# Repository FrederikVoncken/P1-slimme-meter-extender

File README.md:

# P1-slimme-meter-extender
Extending the range for a P1 slimmer meter connection and even making it possible to connect multiple receivers (having their own data enable).
***

The inside of the P1 communication part.

See also 
[Wiki P1-poort](https://nl.wikipedia.org/wiki/P1-poort) and [DSMR P1 Companion Standard 5.0.2](https://www.netbeheernederland.nl/publicatie/dsmr-502-p1-companion-standard)
***
The schematic shows the extension of the Smartmeter P1 port to
* 2 (isolated) P1 outputs
* 2 P1 output extenders (RS485) to multiple meters
* Multiple options for isolation and power

See also the Kicad directory for the project and schematic
[Schematic](Kicad/P1SmartMeter.pdf)

The schematic can be extended to more P1 output or more P1 extenders

Images of the Main part, top and back

Images of the extender receiving part, top and back

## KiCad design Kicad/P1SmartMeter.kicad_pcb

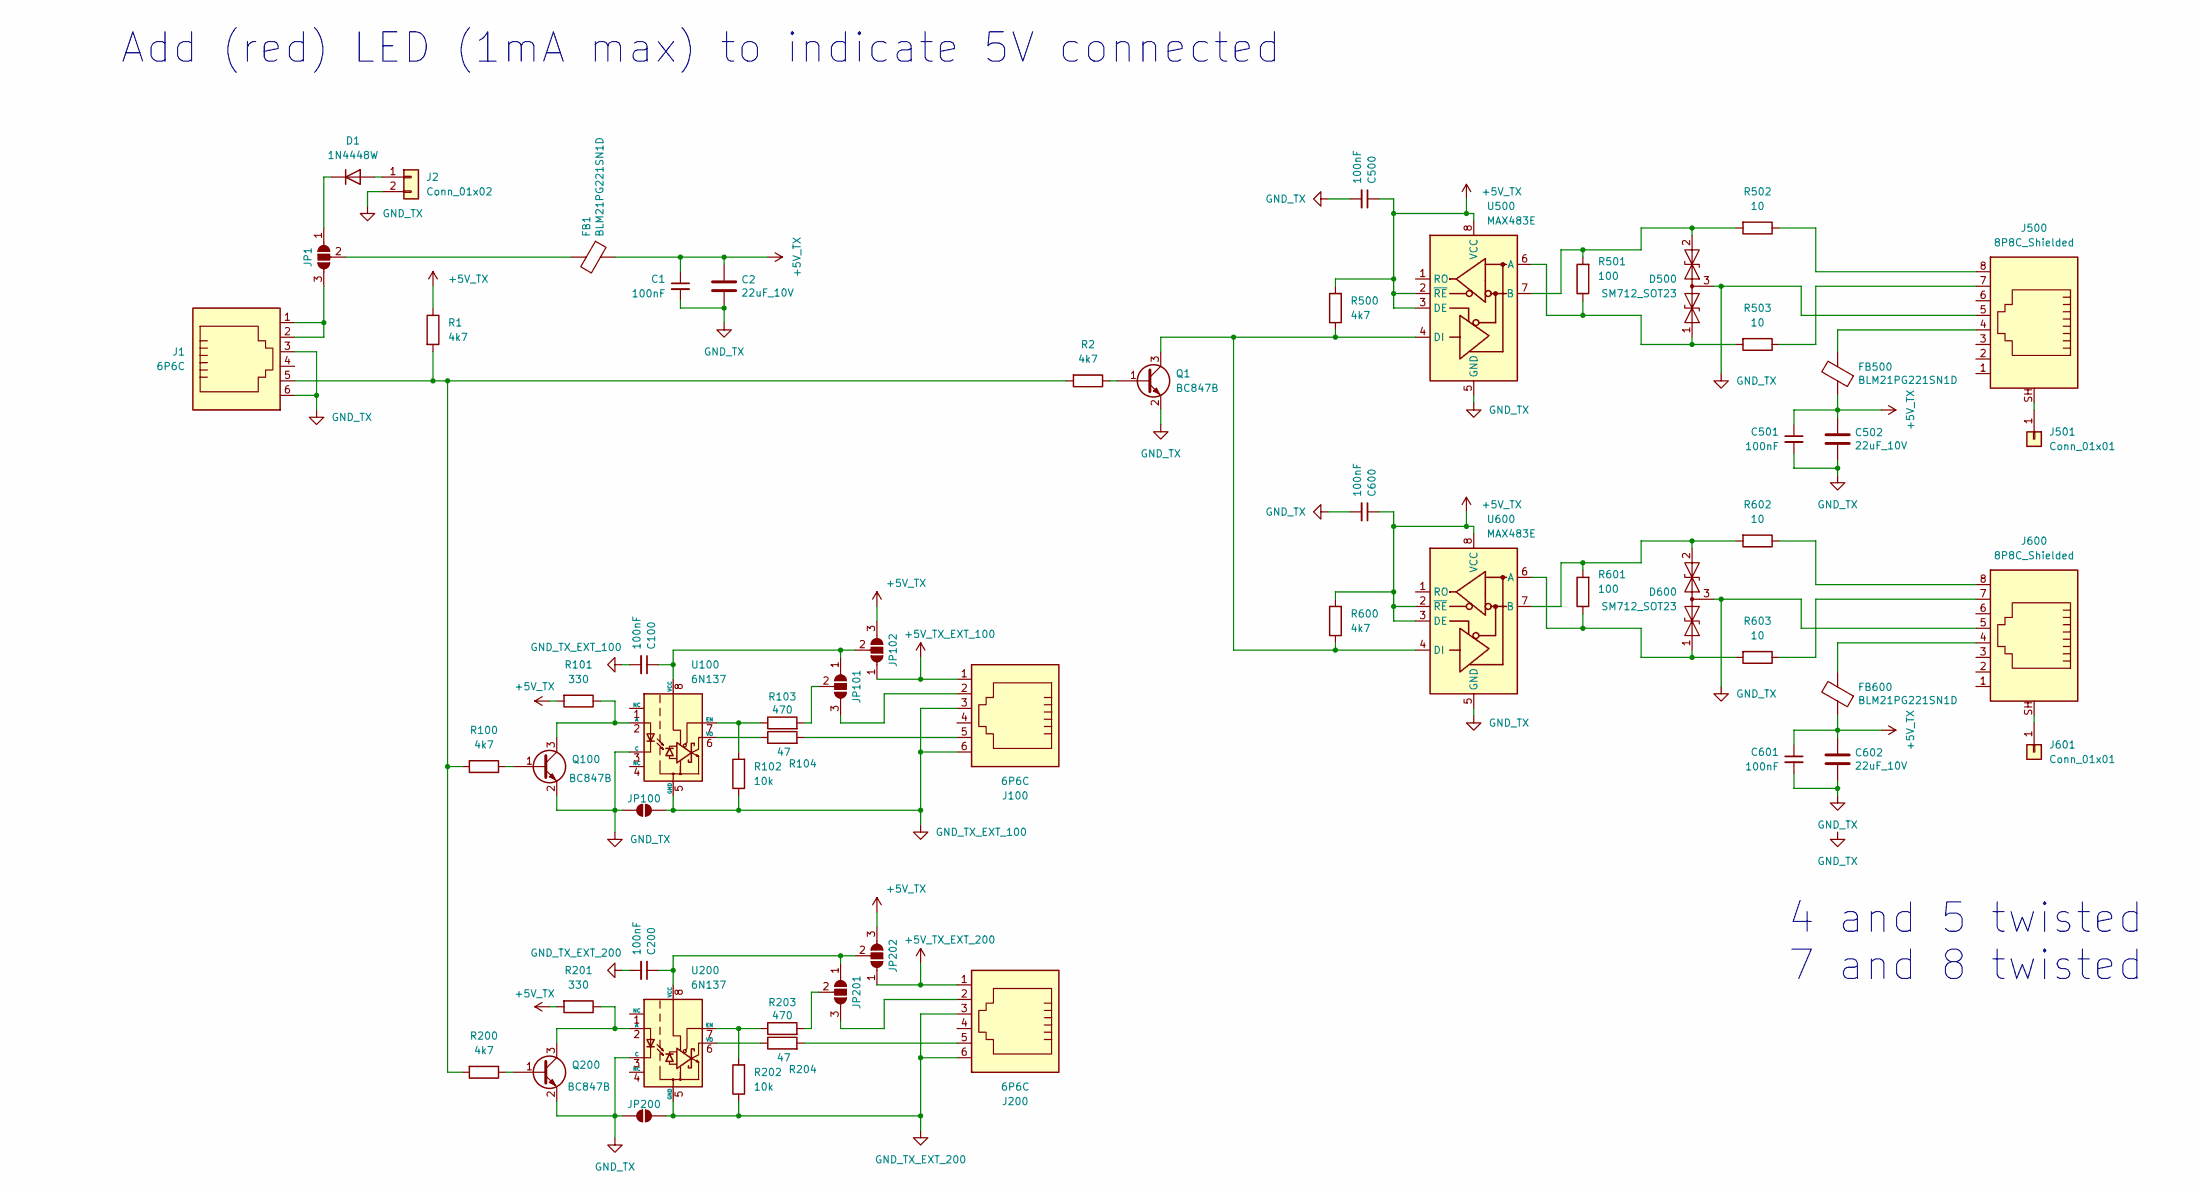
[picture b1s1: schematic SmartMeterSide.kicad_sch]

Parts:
C1, C100, C200, C500, C501, C600, C601: 100nF; C_0805_2012Metric
C2, C502, C602: 22uF_10V; C_1206_3216Metric
D1: 1N4448W; D_SOD-123
D500, D600: SM712_SOT23; SOT-23
FB1, FB500, FB600: BLM21PG221SN1D; R_0805_2012Metric
J1, J100, J200: 6P6C; RJ12_Amphenol_54601-x06_Horizontal
J2: Conn_01x02; PinHeader_1x02_P2.54mm_Vertical
J500, J600: 8P8C_Shielded; RJ45_Ninigi_GE
J501, J601: Conn_01x01; MountingHole_3.2mm_M3_DIN965_Pad_TopBottom
JP1, JP101, JP102, JP201, JP202: SolderJumper_3_Open; SolderJumper-3_P1.3mm_Open_RoundedPad1.0x1.5mm_NumberLabels
JP100, JP200: SolderJumper_2_Open; SolderJumper-2_P1.3mm_Open_RoundedPad1.0x1.5mm
Q1, Q100, Q200: BC847B; SOT-23
R1, R2, R100, R200, R500, R600: 4k7; R_0805_2012Metric
R101, R201: 330; R_0805_2012Metric
R102, R202: 10k; R_0805_2012Metric
R103, R203: 470; R_0805_2012Metric
R104, R204: 47; R_0805_2012Metric
R501, R601: 100; R_0805_2012Metric
R502, R503, R602, R603: 10; R_0805_2012Metric
U100, U200: 6N137; PowerIntegrations_SMD-8
U500, U600: MAX483E; SOIC-8_3.9x4.9mm_P1.27mm

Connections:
+5V_TX: C1.1, C2.1, C500.1, C501.1, C502.1, C600.1, C601.1, C602.1, FB1.1, FB500.1, FB600.1, JP102.3 (B), JP202.3 (B), R1.1, R101.2, R201.2, R500.2, R600.2, U500.2 (~RE), U500.3 (DE), U500.8 (VCC), U600.2 (~RE), U600.3 (DE), U600.8 (VCC)
+5V_TX_EXT_100: J100.1, JP102.1 (A)
+5V_TX_EXT_200: J200.1, JP202.1 (A)
GND_TX: C1.2, C2.2, C500.2, C501.2, C502.2, C600.2, C601.2, C602.2, D500.3 (common), D600.3 (common), J1.3, J1.6, J2.2, J500.5, J600.5, JP100.1 (A), JP200.1 (A), Q1.2 (E), Q100.2 (E), Q200.2 (E), U100.3 (C), U200.3 (C), U500.5 (GND), U600.5 (GND)
GND_TX_EXT_100: C100.2, J100.3, J100.6, JP100.2 (B), R102.1, U100.5 (GND)
GND_TX_EXT_200: C200.2, J200.3, J200.6, JP200.2 (B), R202.1, U200.5 (GND)
unnamed: D1.2 (A), J2.1
unnamed: D1.1 (K), JP1.1 (A)
unnamed: D500.1 (A1), R501.1, R503.2, U500.6 (A)
unnamed: D500.2 (A2), R501.2, R502.2, U500.7 (B)
unnamed: D600.1 (A1), R601.1, R603.2, U600.6 (A)
unnamed: D600.2 (A2), R601.2, R602.2, U600.7 (B)
unnamed: FB500.2, J500.4
unnamed: FB600.2, J600.4
unnamed: J1.5, R1.2, R2.2, R100.2, R200.2
unnamed: J100.5, R104.2
unnamed: J200.5, R204.2
unnamed: J500.7, R503.1
unnamed: J500.8, R502.1
unnamed: J500.SH, J501.1
unnamed: J600.7, R603.1
unnamed: J600.8, R602.1
unnamed: J600.SH, J601.1
unnamed: J1.1, J1.2, JP1.3 (B)
unnamed: FB1.2, JP1.2 (C)
unnamed: C100.1, JP101.1 (A), JP102.2 (C), U100.8 (VCC)
unnamed: J100.2, JP101.3 (B)
unnamed: JP101.2 (C), R103.2
unnamed: C200.1, JP201.1 (A), JP202.2 (C), U200.8 (VCC)
unnamed: J200.2, JP201.3 (B)
unnamed: JP201.2 (C), R203.2
unnamed: Q1.1 (B), R2.1
unnamed: Q1.3 (C), R500.1, R600.1, U500.4 (DI), U600.4 (DI)
unnamed: Q100.1 (B), R100.1
unnamed: Q100.3 (C), R101.1, U100.2 (A)
unnamed: Q200.1 (B), R200.1
unnamed: Q200.3 (C), R201.1, U200.2 (A)
unnamed: R102.2, R103.1, U100.7 (EN)
unnamed: R104.1, U100.6 (VO)
unnamed: R202.2, R203.1, U200.7 (EN)
unnamed: R204.1, U200.6 (VO)

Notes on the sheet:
Add (red) LED (1mA max) to indicate 5V connected
4 and 5 twisted 7 and 8 twisted

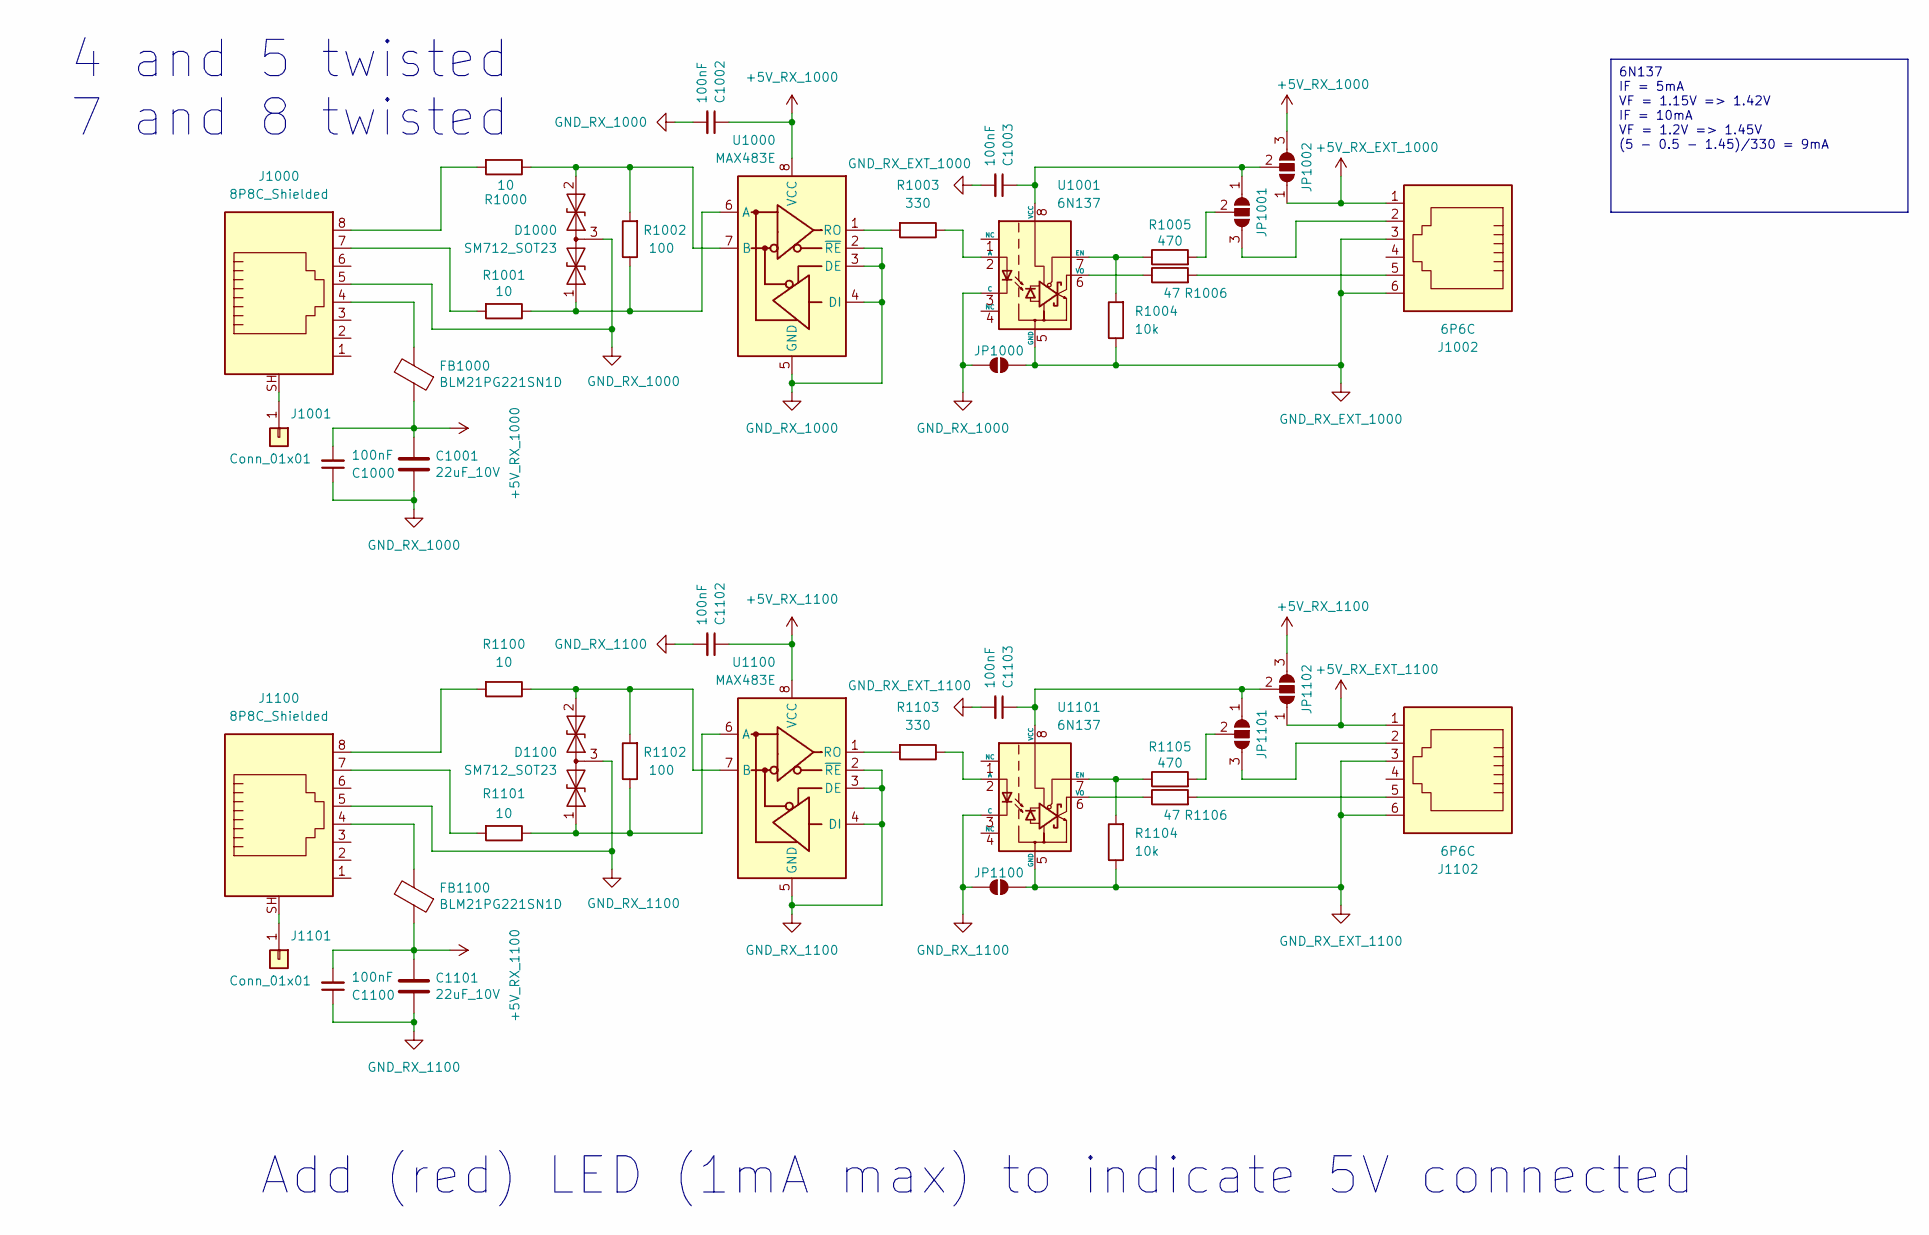
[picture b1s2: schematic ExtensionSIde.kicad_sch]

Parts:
C1000, C1002, C1003, C1100, C1102, C1103: 100nF; C_0805_2012Metric
C1001, C1101: 22uF_10V; C_1206_3216Metric
D1000, D1100: SM712_SOT23; SOT-23
FB1000, FB1100: BLM21PG221SN1D; R_0805_2012Metric
J1000, J1100: 8P8C_Shielded; RJ45_Ninigi_GE
J1001, J1101: Conn_01x01; MountingHole_3.2mm_M3_DIN965_Pad_TopBottom
J1002, J1102: 6P6C; RJ12_Amphenol_54601-x06_Horizontal
JP1000, JP1100: SolderJumper_2_Open; SolderJumper-2_P1.3mm_Open_RoundedPad1.0x1.5mm
JP1001, JP1002, JP1101, JP1102: SolderJumper_3_Open; SolderJumper-3_P1.3mm_Open_RoundedPad1.0x1.5mm_NumberLabels
R1000, R1001, R1100, R1101: 10; R_0805_2012Metric
R1002, R1102: 100; R_0805_2012Metric
R1003, R1103: 330; R_0805_2012Metric
R1004, R1104: 10k; R_0805_2012Metric
R1005, R1105: 470; R_0805_2012Metric
R1006, R1106: 47; R_0805_2012Metric
U1000, U1100: MAX483E; SOIC-8_3.9x4.9mm_P1.27mm
U1001, U1101: 6N137; PowerIntegrations_SMD-8

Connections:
+5V_RX_1000: C1000.2, C1001.1, C1002.1, FB1000.1, JP1002.3 (B), U1000.8 (VCC)
+5V_RX_1100: C1100.2, C1101.1, C1102.1, FB1100.1, JP1102.3 (B), U1100.8 (VCC)
+5V_RX_EXT_1000: J1002.1, JP1002.1 (A)
+5V_RX_EXT_1100: J1102.1, JP1102.1 (A)
GND_RX_1000: C1000.1, C1001.2, C1002.2, D1000.3 (common), J1000.5, JP1000.1 (A), U1000.2 (~RE), U1000.3 (DE), U1000.4 (DI), U1000.5 (GND), U1001.3 (C)
GND_RX_1100: C1100.1, C1101.2, C1102.2, D1100.3 (common), J1100.5, JP1100.1 (A), U1100.2 (~RE), U1100.3 (DE), U1100.4 (DI), U1100.5 (GND), U1101.3 (C)
GND_RX_EXT_1000: C1003.2, J1002.3, J1002.6, JP1000.2 (B), R1004.1, U1001.5 (GND)
GND_RX_EXT_1100: C1103.2, J1102.3, J1102.6, JP1100.2 (B), R1104.1, U1101.5 (GND)
unnamed: D1000.1 (A1), R1001.1, R1002.1, U1000.6 (A)
unnamed: D1000.2 (A2), R1000.1, R1002.2, U1000.7 (B)
unnamed: D1100.1 (A1), R1101.1, R1102.1, U1100.6 (A)
unnamed: D1100.2 (A2), R1100.1, R1102.2, U1100.7 (B)
unnamed: FB1000.2, J1000.4
unnamed: FB1100.2, J1100.4
unnamed: J1000.7, R1001.2
unnamed: J1000.8, R1000.2
unnamed: J1000.SH, J1001.1
unnamed: J1002.5, R1006.2
unnamed: J1100.7, R1101.2
unnamed: J1100.8, R1100.2
unnamed: J1100.SH, J1101.1
unnamed: J1102.5, R1106.2
unnamed: C1003.1, JP1001.1 (A), JP1002.2 (C), U1001.8 (VCC)
unnamed: J1002.2, JP1001.3 (B)
unnamed: JP1001.2 (C), R1005.2
unnamed: C1103.1, JP1101.1 (A), JP1102.2 (C), U1101.8 (VCC)
unnamed: J1102.2, JP1101.3 (B)
unnamed: JP1101.2 (C), R1105.2
unnamed: R1003.2, U1000.1 (RO)
unnamed: R1003.1, U1001.2 (A)
unnamed: R1004.2, R1005.1, U1001.7 (EN)
unnamed: R1006.1, U1001.6 (VO)
unnamed: R1103.2, U1100.1 (RO)
unnamed: R1103.1, U1101.2 (A)
unnamed: R1104.2, R1105.1, U1101.7 (EN)
unnamed: R1106.1, U1101.6 (VO)

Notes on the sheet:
6N137 IF = 5mA VF = 1.15V => 1.42V IF = 10mA VF = 1.2V => 1.45V (5 - 0.5 - 1.45)/330 = 9mA
4 and 5 twisted 7 and 8 twisted
Add (red) LED (1mA max) to indicate 5V connected

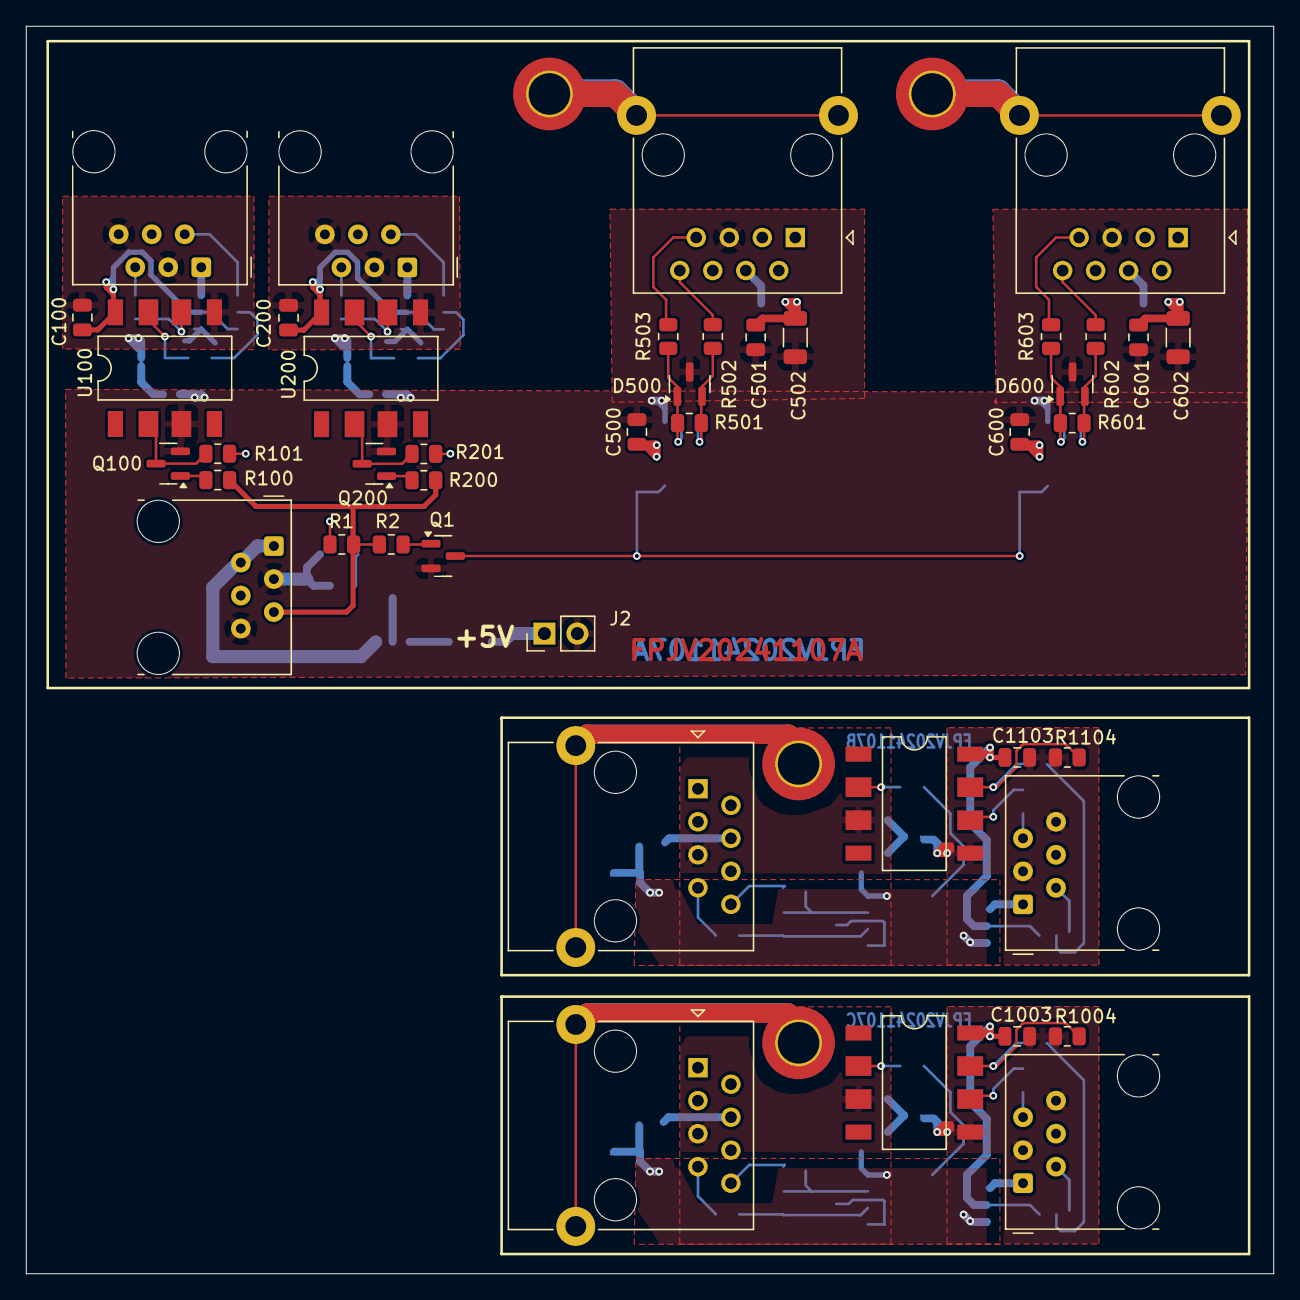
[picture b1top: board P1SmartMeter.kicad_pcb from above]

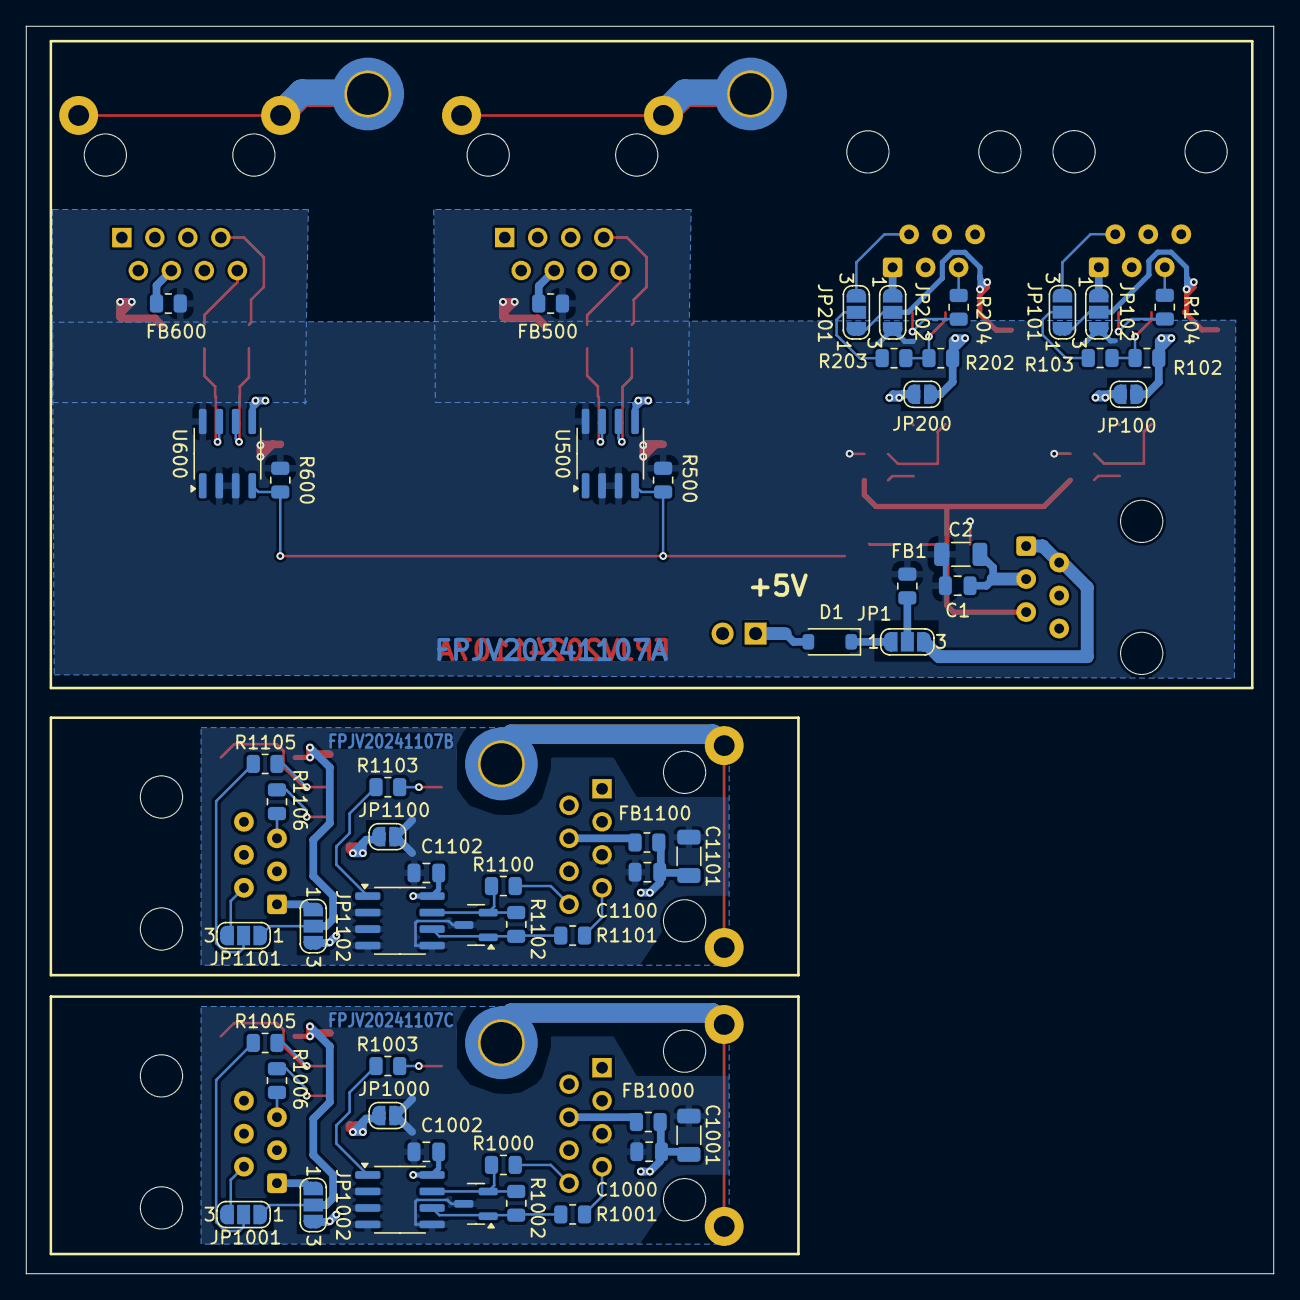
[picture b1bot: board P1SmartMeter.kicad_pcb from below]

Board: 2 copper layers, 96.0 x 96.0 mm, 100 parts (53 on the bottom side), 77 nets.

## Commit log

2024-08-17 Adding documentation
2025-06-23 Updating with schematics and info
